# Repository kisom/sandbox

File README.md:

## AQE: A Query Engine

This is an implementation of a knowledge base, hacked together in Python
3 (it won't work in Python 2 for reasons of modules) for now to quickly
iterate on ideas.

There are a few key points:

+ A `KnowledgeBase` contains facts.
+ A fact is a tuple: (relationship, subject, object). For example,
  `('is', 'sky', 'blue')`.
+ A `KnowledgeBase` has three core methods: ask, retract, and tell.
+ The `ask` method queries the `KnowledgeBase` to ascertain whether
  a fact is true. Either the subject or the object may be `None`,
  in which case all satisifiable facts are returned.
+ The `retract` method tells the `KnowledgeBase` that the fact is
  no longer true. If it's rainy, we might retract our fact about the
  sky being blue.
+ The `tell` method tells the `KnowledgeBase` that the fact is
  now true. For example, if it's rainy (and we've retracted the previous
  'sky is blue' fact), we might tell the `KnowledgeBase` that
  `('is', 'sky', 'grey')`.
+ A `KnowledgeBase` can also perform substitutions.
+ An action contains positive and negative preconditions, retractions,
  and updates. The positive condition list contains facts that must
  be true for a knowledge base, and the negative condition list contains
  facts that must be false. If these preconditions hold, the retractions
  are applied, followed by the updates.
+ See `test_actions.py` for an example.

### Limitations

+ Singleton facts aren't supported; that is, there is no way to make a
  `KnowledgeBase` assert that there is only one relationship → subject
  mapping. For example, the `KnowledgeBase` will admit that
  `('is', 'shrödingers cat', 'alive')` and
  `('is', 'schrödingers cat', 'dead')` are both true simultaneously.

### TODO

+ Inference: given a list of actions, how to go from one state to
  another. The first step would be single-step, then integrating
  a search into the inference.
+ Rewrite in C++?

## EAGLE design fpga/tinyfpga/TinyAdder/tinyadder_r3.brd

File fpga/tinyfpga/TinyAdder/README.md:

TinyAdder
========

TinyAdder is a 4-bit adder built on the TinyFPGA BX. It connects four
slide switches (I wanted actual toggle switches, but that's how it goes)
to a pair of 7-segment LCD displays.

Code organisation
-----------------

Currently there are two modules:

+ SegmentLCD: a little awkwardly named due to the naming constraints,
  but this takes a 4-bit input number and outputs a 7-bit output. The
  hookup requirements are described in the module comments.
+ TinyAdder: This is the top-level adder.

Hardware revisions
------------------

+ rev1 (2018-12-22)
+ rev2 (2018-12-22): realised that the LCDs were missing resistors;
  I had been looking at a tutorial that used a shift register; the shift
  register apparently had an internal current limiter so I assumed the
  LCDs didn't need them. This was wrong. Fortunately I was able to cancel
  the rev1 order before it went out.
+ rev3 (2018-12-28): after breadboarding the push button, I realised
  I'd messed up the schematic (and accordingly, the board) by wiring
  both ends of the push buttons to Vcc, which... isn't very useful at
  all. I fixed it, but not before the rev2 was sent to the fab.

TODO
----

+ I'd like to have the two displays show the two numbers before adding
  them. The 'hi' display could show the first addend, and the 'low' could
  show the second addend, with live updating.

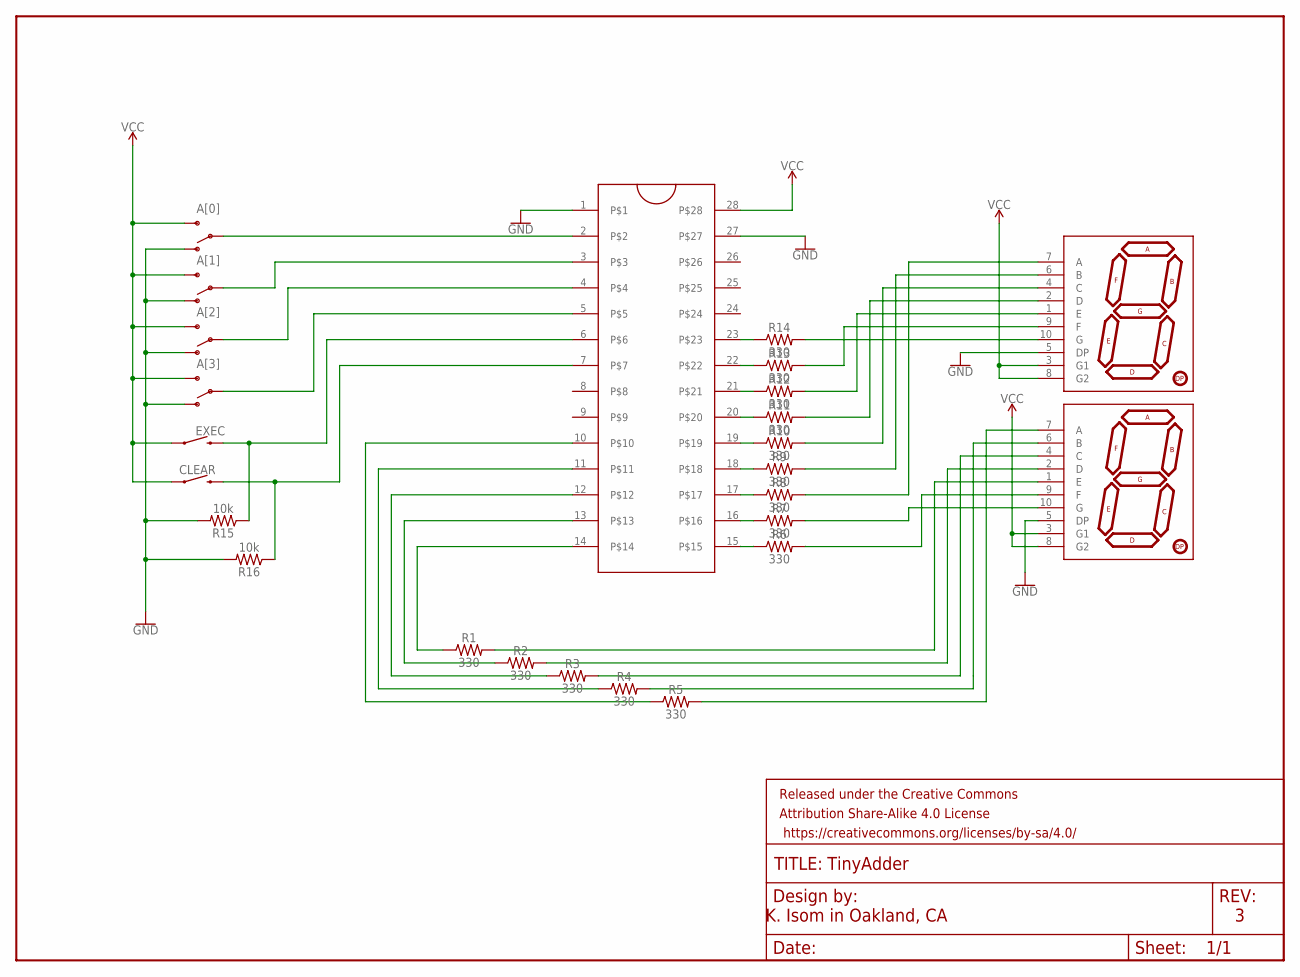
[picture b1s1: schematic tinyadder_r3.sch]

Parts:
A[0], A[1], A[2], A[3]: SWITCH-SPDT-PTH-11.6X4.0MM; SWITCH_SPDT_PTH_11.6X4.0MM
CLEAR: MOMENTARY-SWITCH-SPST-PTH-6.0MM; TACTILE_SWITCH_PTH_6.0MM
EXEC: MOMENTARY-SWITCH-SPST-PTH-6.0MM; TACTILE_SWITCH_PTH_6.0MM
FRAME1: FRAME-LETTER; CREATIVE_COMMONS
J1: ZIFSOCKET-28-3"; DIL28-3-ZIF_SOCKET
R1, R2, R3, R4, R5, R6, R7, R8, R9, R10, R11, R12, R13, R14: 330; AXIAL-0.3
R15, R16: 10k; AXIAL-0.3
U$1, U$2: YSD-1601AR4B-8; 7-SEGMENT-1"PTH

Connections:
GND: A[0].1 (O), A[1].1 (O), A[2].1 (O), A[3].1 (O), J1.1, J1.27, R15.P$2 (2), R16.P$2 (2), U$1.5 (DP), U$2.5 (DP)
unnamed: A[0].2, J1.2
unnamed: A[1].2, J1.3
unnamed: A[2].2, J1.4
unnamed: A[3].2, J1.5
unnamed: EXEC.3 (2), J1.6, R15.P$1 (1)
unnamed: CLEAR.3 (2), J1.7, R16.P$1 (1)
unnamed: J1.10, R5.P$1 (1)
unnamed: J1.11, R4.P$1 (1)
unnamed: J1.12, R3.P$1 (1)
unnamed: J1.13, R2.P$1 (1)
unnamed: R1.P$2 (2), U$2.1 (E)
unnamed: R6.P$2 (2), U$2.9 (F)
unnamed: R7.P$2 (2), U$2.10 (G)
unnamed: R8.P$2 (2), U$1.7 (A)
unnamed: R9.P$2 (2), U$1.6 (B)
unnamed: R10.P$2 (2), U$1.4 (C)
unnamed: R11.P$2 (2), U$1.2 (D)
unnamed: R12.P$2 (2), U$1.1 (E)
unnamed: R13.P$2 (2), U$1.9 (F)
unnamed: J1.15, R6.P$1 (1)
unnamed: J1.14, R1.P$1 (1)
unnamed: R2.P$2 (2), U$2.2 (D)
unnamed: R3.P$2 (2), U$2.4 (C)
unnamed: R4.P$2 (2), U$2.6 (B)
unnamed: R5.P$2 (2), U$2.7 (A)
unnamed: J1.16, R7.P$1 (1)
unnamed: J1.17, R8.P$1 (1)
unnamed: J1.18, R9.P$1 (1)
unnamed: J1.19, R10.P$1 (1)
unnamed: J1.20, R11.P$1 (1)
unnamed: J1.21, R12.P$1 (1)
unnamed: J1.22, R13.P$1 (1)
unnamed: J1.23, R14.P$1 (1)
unnamed: R14.P$2 (2), U$1.10 (G)
VCC: A[0].3 (S), A[1].3 (S), A[2].3 (S), A[3].3 (S), CLEAR.1, EXEC.1, J1.28, U$1.3 (G1), U$1.8 (G2), U$2.3 (G1), U$2.8 (G2)

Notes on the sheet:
TinyAdder
K. Isom in Oakland, CA

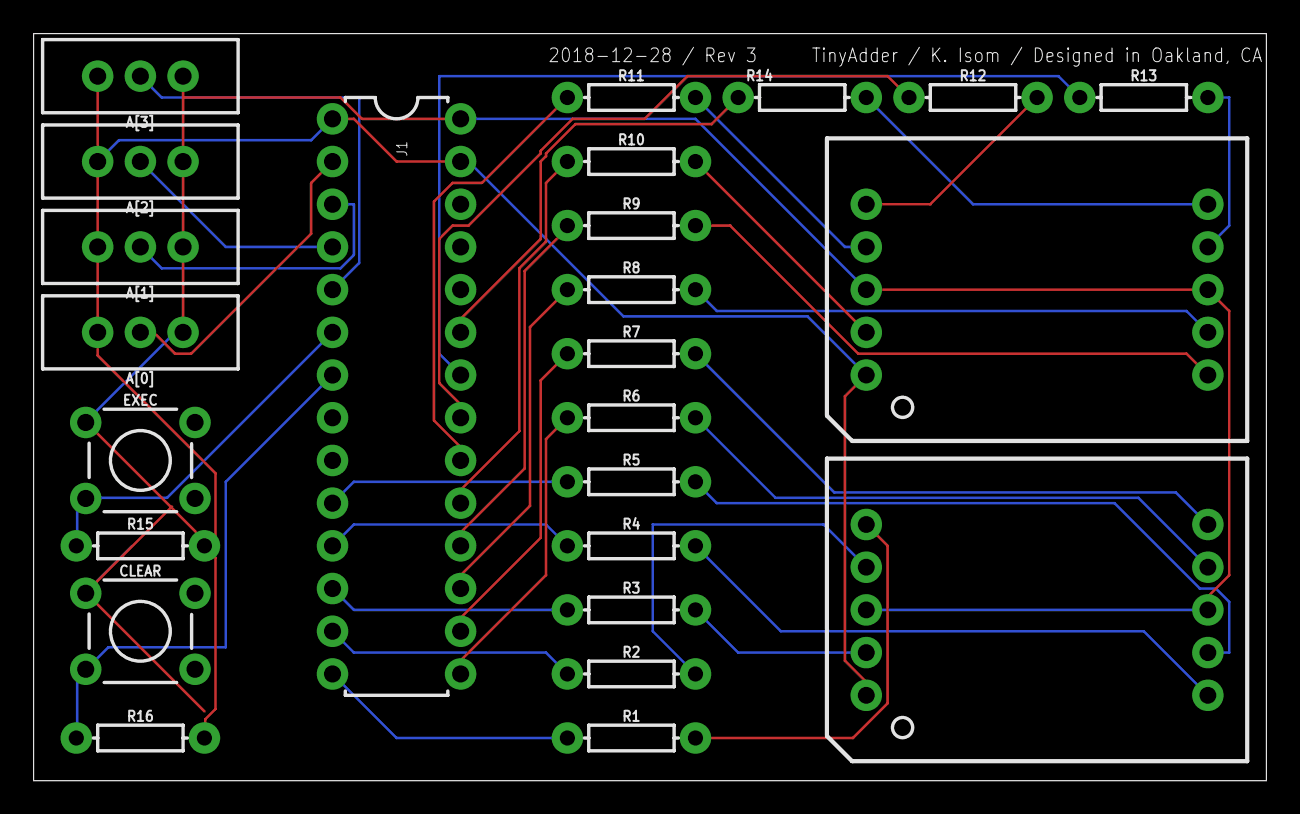
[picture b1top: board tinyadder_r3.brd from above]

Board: 2 copper layers, 73.3 x 44.4 mm, 26 parts (0 on the bottom side), 36 nets.

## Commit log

2017-11-09 Initial import.
2017-11-09 Dumping some WIP stuff.
2017-11-09 Add chromebook dev env stuff.
2017-12-19 Start work on chapter 1 exercises.
2017-12-19 Switch to autotools.
2017-12-19 Work through exercise 1.3.
2017-12-19 Ignore automake stuff.
2017-12-19 Adding exercise descriptions.
2017-12-19 Automake the data files.
2017-12-19 NB broken. Working on the list implementation.
2017-12-20 build system and framework for list
2017-12-21 C++ stuff sorted out.
2017-12-21 SimpList moved to header-only implementation.
2017-12-21 Start simple USet implementation.
2017-12-21 Update build and basic DS test framework.
2017-12-21 Finish SimpUSet implementation.
2017-12-21 Add List benchmark.
2017-12-22 Add SSet implementation.
2017-12-22 Adding some performance improvement ideas for ex 1.7.
2017-12-22 Add linked list and benchmarks.
2017-12-22 Add perf data.
2017-12-22 Add perf text file.
2017-12-22 Add docker container.
    Because clang is outdated on many of my other machines.
2018-01-17 LPN: reorg, split notes from exocortex page.
    The exocortex page was getting unwieldy, this makes more sense.
2018-01-17 Add finished ch03 exercises.
2018-01-17 Add practical no. 1 and 2 from chapter 3.
2018-01-18 Finish ch03 exercises.
2018-01-19 Add ch04, start working on ch05.
2018-01-19 Finish ch05 practical.
2018-01-26 Start chapter 6.
2018-01-26 Add pamphlet against r start.
2018-01-31 Add anagram.lisp.
2018-01-31 Add gitignore.
2018-01-31 Update README.
2018-02-01 Add ng build file.
2018-02-01 Add ods link.
2018-02-01 Add (disabled) additional targets.
2018-02-01 Add link to the basement.
2018-02-07 Start chapter 2, switch to ng-backed build.
2018-02-07 Ignore ng/ninja artifacts.
2018-02-07 Add practical prolog start.
2018-02-07 Nominally start ODS chapter 2.
2018-02-08 More chapter 2 work.
2018-02-08 More stuff on chapter 2's array stack.
2018-02-20 Finish ArrayStack.
2018-02-21 Start working on ArrayDeque.
2018-02-21 Finish ArrayDeque.
2018-02-21 Start kf (kyle's forth)
    Here we go with another pass at writing a Forth.
2018-02-21 kf: linux console for I/O
2018-02-21 Track current progress.
2018-03-05 ods: Working on DualArrayDeque.
2018-03-06 ods: fix size in DualArrayDeque balance().
2018-03-06 Start bluepill skeleton and blinky project.
2018-03-06 blue-pill: update skeleton/blinky Makefile
2018-03-06 bluepill: working on header file
2018-03-07 bluepill: start HAL, update skeleton.
2018-03-07 blue-pill: start the startup code
    no idea if this works yet
2018-03-07 blue-pill: more draugr cleanups
2018-03-08 sandbox: update READMEs for projects
2018-03-08 ods: update data automakefile
2018-03-08 blue-pill: convert blinky to startup.s boot.
2018-03-08 blue-pill: fix bootloader.
2018-03-08 blue-pill: cleaning some stuff up
2018-03-13 blue-pill: fix linker scripts and asm led turnon
2018-03-13 blue-pill: copying linker script over
2018-03-15 ion: first pass at stretchy buffers.
    However, len is expressed as number of elements, and capacity as
    number of bytes.
2018-03-15 ion: start implementing stretchy buffers via the video.
2018-03-23 bitwise: add progress on ion
2018-03-26 bitwise: another three minutes of video on the bus.
2018-03-27 bitwise: more work on ion
2018-03-28 bitwise: finish day 2
2018-03-28 bitwise: ion release doesn't need a different target name
2018-04-07 par: add proplogic
2018-04-07 misc: starting Turing Machine in Racket.
2018-04-07 misc: add simple turing machine from DAS.
2018-04-10 adsep: start algorithms + data structs = programs.
2018-04-10 various updates
2018-04-10 adsep: some lunch progress
2018-04-13 algotune: finish library.
2018-04-13 algotune: start work on algotune.
    This is a library for stress testing algorithms problems.
2018-04-13 algotune: renamed directory to match library name
2018-04-13 algotune: make reseed public.
2018-04-27 pio: start platformIO projects
2018-06-05 misc/kforth: Initial import.
2018-06-05 misc/kforth: Starting work on the parser.
2018-06-05 misc/kforth: Finish parsing.
2018-06-05 misc/kforth: Part 0x04 - parsing numerics.
2018-06-05 misc/kforth: Iron out numeric issues.
2018-06-05 misc/kforth: but what were you feeling
2018-06-05 misc/kforth: spello
2018-06-05 misc/kforth: Start command processing.
2018-06-05 misc/kforth: Interpreter writeup, code cleanups.
2018-06-05 misc/kforth: rst fixups
2018-06-05 misc/kforth: Add system status, work on vocab, better write_num.
    - Now system structure includes a status variable and an associated
    function for writing the status out.
    - Adding more words to the builtin dictionary.
    - write_num round 3.
    - Include option to not print the stack each iteration.
2018-06-05 misc/kforth: Filling out more words.
2018-06-05 misc/kforth: Add forth standard 83
2018-06-05 misc/kforth: Adding stats.
2018-06-05 misc/kforth: Mostly finished with nucleus layer.
2018-06-05 misc/kforth: Notionally start this next writeup.
2018-06-05 misc/kforth: Store proper dictionary address.
2018-06-05 misc/kforth: Starting work on writeup.
2018-06-05 misc/kforth: Finish part 0x07 writeup.
2018-06-05 misc/kforth: Minor update to part 0x07 writeup.
2018-06-05 misc/kforth: Move previous work to v1.
2018-06-05 misc/kforth: Start over.
2018-06-05 misc/kforth: Restart the world.
2018-06-05 misc/kforth: More work.
2018-06-05 misc/kforth: Fix a bunch of bugs from part 0x08.
2018-06-05 misc/kforth: Add new part.
2018-06-05 misc/kforth: Add link to tag.
2018-06-05 django: finish tutorial
2018-06-05 misc/aqe: thinking about inference
2018-06-05 Link to sketchbooks, devlog, and notebook.
2018-06-05 django: Moving on to tutorial 5.
    I'm a moron.
2018-06-05 Add Jupyter notebook with some examples.
2018-06-05 misc/numworks: add echelon script for numworks.
2018-06-05 django: Tutorial 6.
2018-06-05 misc/aqe: Initial import.
2018-06-05 django: mysite/working on tutorial 4
    during switch to generic views, blah blah blah
2018-06-05 django: complete tutorial #5
2018-06-05 django: starting the django tutorial
2018-06-05 django: finish tutorial #3
2018-06-11 Fix up bad git subtree import.
2018-06-11 Add first QC experiments.
    Bell states in the Microsoft Quantum SDK and Rigetti's pyQuil.
2018-06-11 qc: add README.
2018-08-21 Start Rust OS stuff.
2018-08-30 Start homework 5.
2018-09-04 programming rust: finish chapter 2.
2018-09-04 lr -> pr
2018-09-06 ostep: add hw5
2018-11-13 Start shipping problem.
2018-12-28 fpga: add TinyAdder rev1
2018-12-28 TinyAdder: add EAGLE files.
2018-12-28 TinyFPGA: add beacon
2018-12-29 Update FPGA experiments.
    + Separate out into per-board directories.
    + Add icestick hello world.
    + Add TinyFPGA hello world, beacon, button-triggered LED, and TinyAdder.
    + Add platform constraint files for the iCEStick and TinyFPGA.
2018-12-29 Add GEB pq checker.
2018-12-29 Add CMSIS bluepill blink.
2018-12-29 TinyFPGA: add button-toggled LED.
2018-12-29 TinyFPGA/btled: a comment.
2018-12-29 TinyAdder: Add docs, organise things, updated EAGLE files.
2018-12-29 TinyAdder: remove unused pins from constraints, add Makefile.
2018-12-29 TinyAdder: clean up top-level.
2018-12-29 TinyFPGA: update name of verilog "sketch".
2018-12-29 Remove unused register.
2018-12-29 pio: nrf52 test blinks LED.
2018-12-29 fpga: add iCEStick btled example.
2018-12-31 pio: add bluepill blink.
2019-01-02 fpga: 7-segment test on TinyFPGA.
2019-01-03 fpga: add icestick segment LCD demo.
2019-01-03 bluepill: add usbcdc example
2019-01-03 Add NumberDisplay and SwitchLED.
2019-02-17 Add perlin noise implementation.
2019-04-22 Start programming erlang.
2019-04-22 Updating PE.
2019-04-22 Working through PE.
2019-04-22 PE: Starting ch4 exercises.
2019-04-23 more erlang
    rip joe :(
2019-04-23 add term stashing
    rip joe :(
2019-04-24 From scratch forth text editor.
2019-04-24 Add RGB.
2019-04-24 pe: add compiled funs.
2019-04-24 bus experiments
2019-04-25 slow hacks
2019-04-25 Fix inverted logic case in file uploads.
2019-04-25 Working on chapter 7 exercises.
2019-04-26 Fix permissions.
    Somehow this ended up 0777. It's now 664.
2019-04-26 Finish chapter 7 code.
2019-04-26 Add a note.
2019-04-26 Finishing up part 1.
2019-04-29 Commit chapter 12 stuff from last night.
2019-04-30 Start ring stuff.
2019-06-15 Adding some erlang stuff.
2019-09-16 add chapter 2 questions
2019-09-16 Add two examples from ch2.
2019-09-16 ignore some ada build cruft
2019-09-17 stuff
2019-09-24 clean up PrintRoots2.

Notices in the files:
parts and their libraries:
SparkFun-Switches: Licensing: Creative Commons ShareAlike 4.0 International - https://creativecommons.org/licenses/by-sa/4.0
SparkFun-Aesthetics: Released under the Creative Commons Attribution Share-Alike 4.0 License
SparkFun-Aesthetics: https://creativecommons.org/licenses/by-sa/4.0
